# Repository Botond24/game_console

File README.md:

# game_console
name tbd

## Firmware Block Diagram

```mermaid
flowchart TD
    SD[(SD Card\nFAT32)]

    subgraph Core0 ["Core 0 -- Bootloader"]
        Menu["Menu\n- Lists .bin files from SD\n- Selects & launches game"]
        Overlay["Overlay Loop\n- Monitors A+B+UP\n- Kills game, returns to menu"]
        HAL["HAL\n- draw_pixel()\n- read_input()"]
    end

    subgraph Core1 ["Core 1 -- User Game"]
        Game["Game Binary\n- Loaded into RAM @ 0x20010000\n- Owns its own loop\n- Calls HAL only"]
    end

    subgraph Hardware ["Peripherals"]
        OLED["OLED Display\n(mutex-guarded)"]
        BTN[Buttons]
    end

    SD -->|"Read once at launch"| Menu
    Menu -->|"memcpy to 0x20010000\npush addr via FIFO"| Game
    Menu -->|"starts"| Overlay
    Overlay -->|"rp2040.restartCore1()\non A+B+UP"| Game
    Game -->|"calls"| HAL
    HAL -->|"drawPixel()"| OLED
    HAL -->|"reads"| BTN
```

## Folders

- `bootloader/` - Core bootloader firmware for the RP2040 that runs on Core 0. You don't need to touch this unless you want to.
- `game/` - Template game project structure and example game firmware that runs on Core 1. This is the base template for developing new games.
- `pcb/` - Hardware design files including the KiCad PCB schematic, layout, footprints library, and production files (BOM, positions, netlist).
- `test-games/` - Test games and development utilities for validation and demonstration purposes.

## Notes 

- Everything is incredibly rudimentary and you shouldn't expect us to respond to issues. We welcome contributions though, so if you want to add features or fix bugs, fork the repo and send a PR.
- Add your game to the [discussions tab](https://github.com/CircuitReeRUG/game_console/discussions/4)! We would love to see what you make with this!
- You can tag @frogspyder on the Cover Discord server if you want to chat about anything related to this project and/or drop by in the [Discord thread](https://discord.com/channels/1073220526585159681/1484931557876826284).

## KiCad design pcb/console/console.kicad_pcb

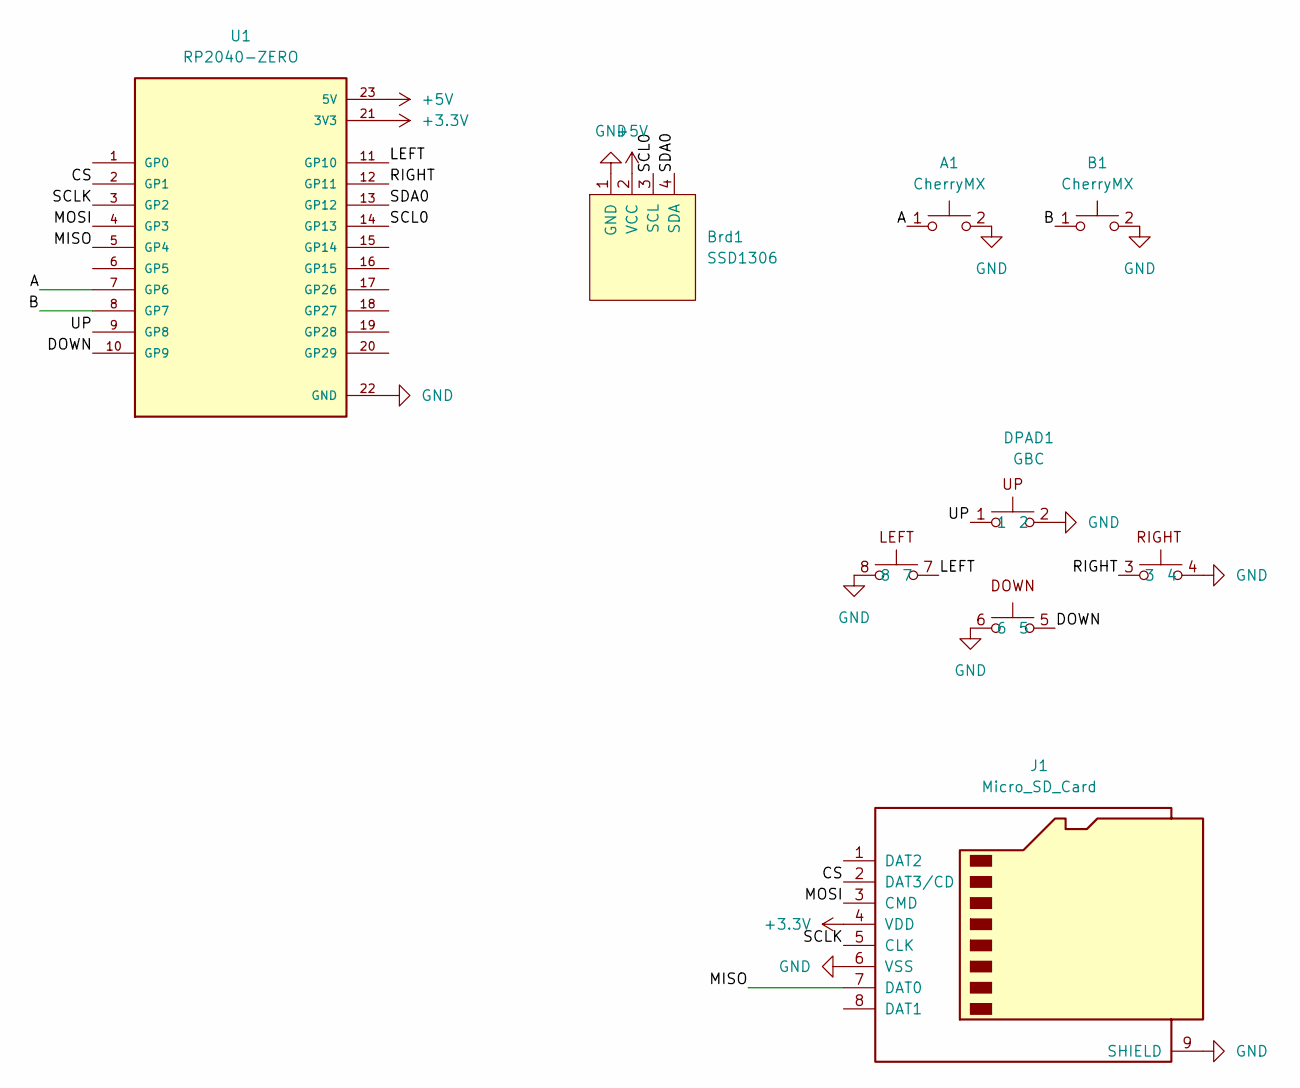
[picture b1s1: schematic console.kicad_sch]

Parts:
A1: CherryMX; CherryMX_1.00u_KailhSocket
B1: CherryMX; CherryMX_1.00u_KailhSocket
Brd1: SSD1306; 128x64OLED
DPAD1: GBC; GBC DPAD
J1: Micro_SD_Card; microSD_HC_Wuerth_693072010801
U1: RP2040-ZERO; MODULE_RP2040-ZERO; PARTREV NA

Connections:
+3.3V: J1.4 (VDD), U1.21 (3V3)
+5V: Brd1.2 (VCC), U1.23 (5V)
/A: A1.1, U1.7 (GP6)
/B: B1.1, U1.8 (GP7)
/CS: J1.2 (DAT3/CD), U1.2 (GP1)
/DOWN: DPAD1.5, U1.10 (GP9)
/LEFT: DPAD1.7, U1.11 (GP10)
/MISO: J1.7 (DAT0), U1.5 (GP4)
/MOSI: J1.3 (CMD), U1.4 (GP3)
/RIGHT: DPAD1.3, U1.12 (GP11)
/SCL0: Brd1.3 (SCL), U1.14 (GP13)
/SCLK: J1.5 (CLK), U1.3 (GP2)
/SDA0: Brd1.4 (SDA), U1.13 (GP12)
/UP: DPAD1.1, U1.9 (GP8)
GND: A1.2, B1.2, Brd1.1 (GND), DPAD1.2, DPAD1.4, DPAD1.6, DPAD1.8, J1.6 (VSS), J1.9 (SHIELD), U1.22 (GND)

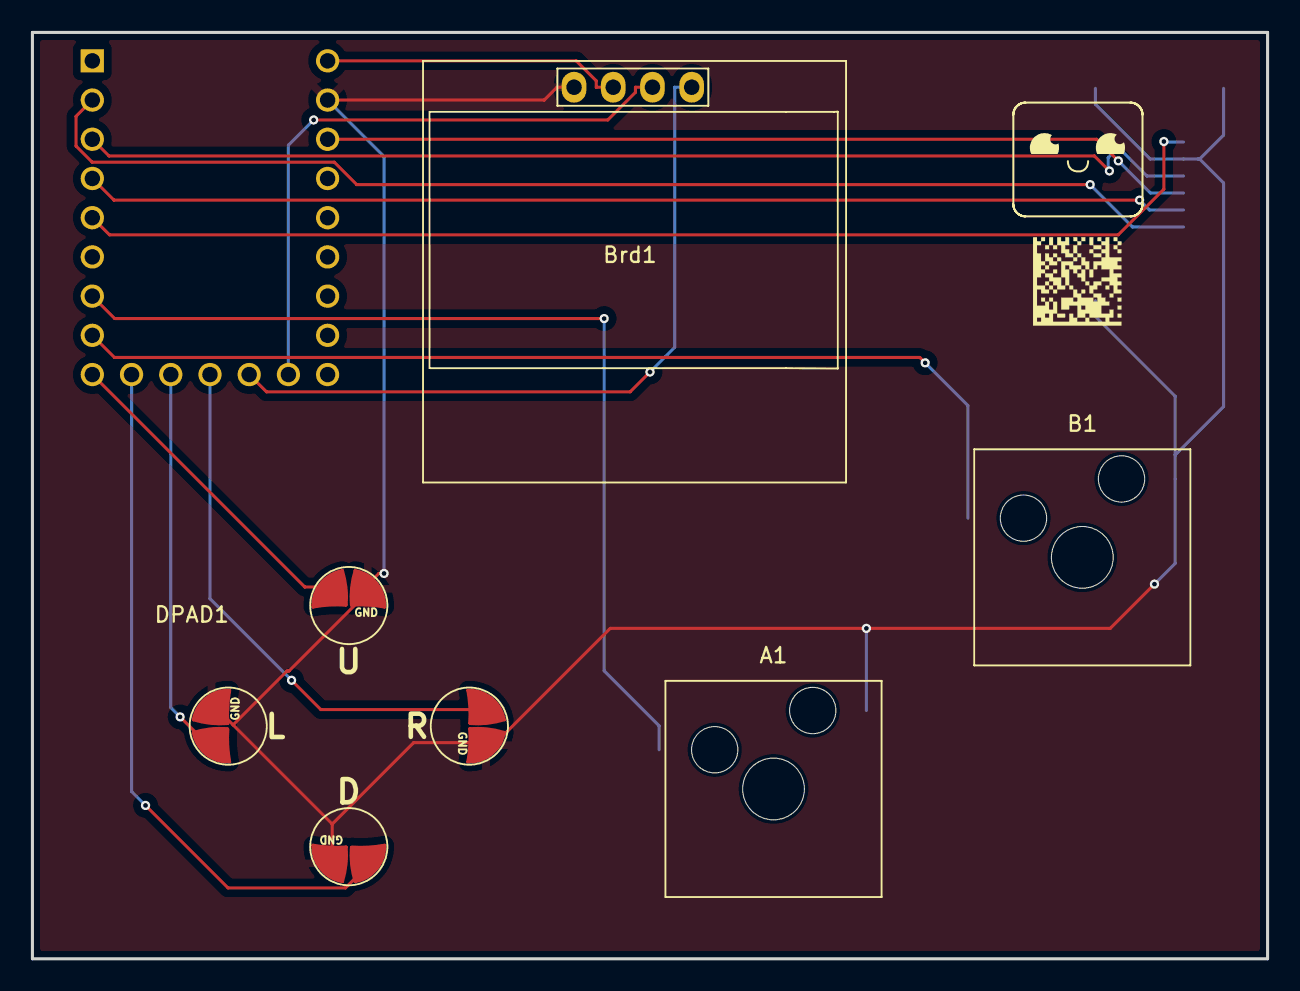
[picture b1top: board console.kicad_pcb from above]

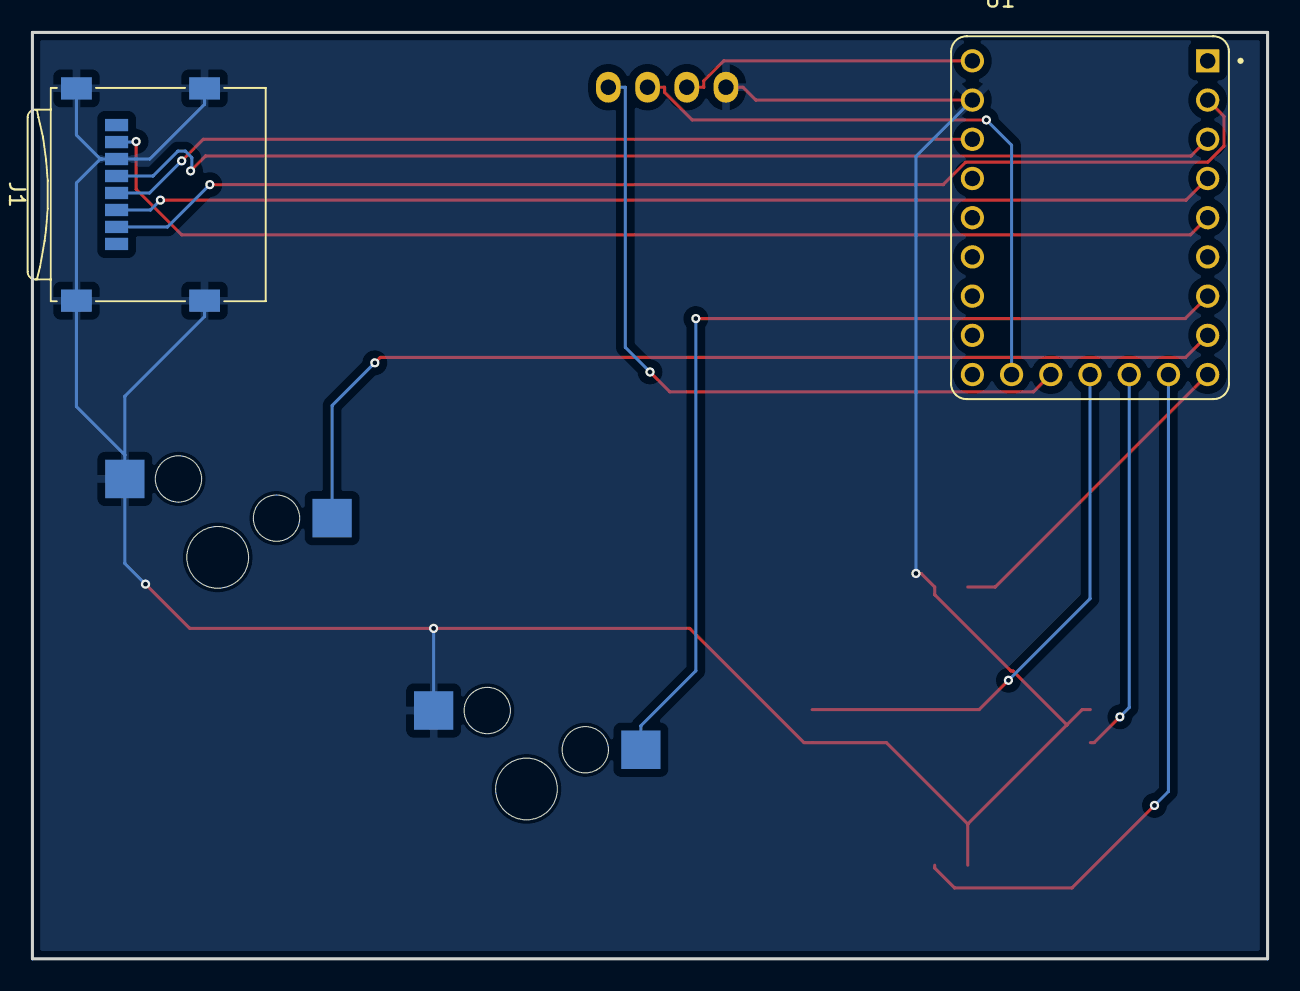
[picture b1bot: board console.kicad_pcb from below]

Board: 2 copper layers, 80.0 x 60.0 mm, 6 parts (2 on the bottom side), 15 nets.

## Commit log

2026-02-28 ordered prototype
2026-03-04 comment test thing for compilation
2026-03-16 Strides
2026-03-21 Move hal to separate files
2026-03-21 Game env
2026-03-21 Rewrite core logic -- kill watchdog
2026-03-21 Vibe coded test game
2026-03-21 Reorg
2026-03-21 reformat and reorg
2026-03-24 deleted a log file that caused an error when pulling
2026-03-25 HAL update
2026-03-27 asdf
2026-03-27 Expose the interface to user
